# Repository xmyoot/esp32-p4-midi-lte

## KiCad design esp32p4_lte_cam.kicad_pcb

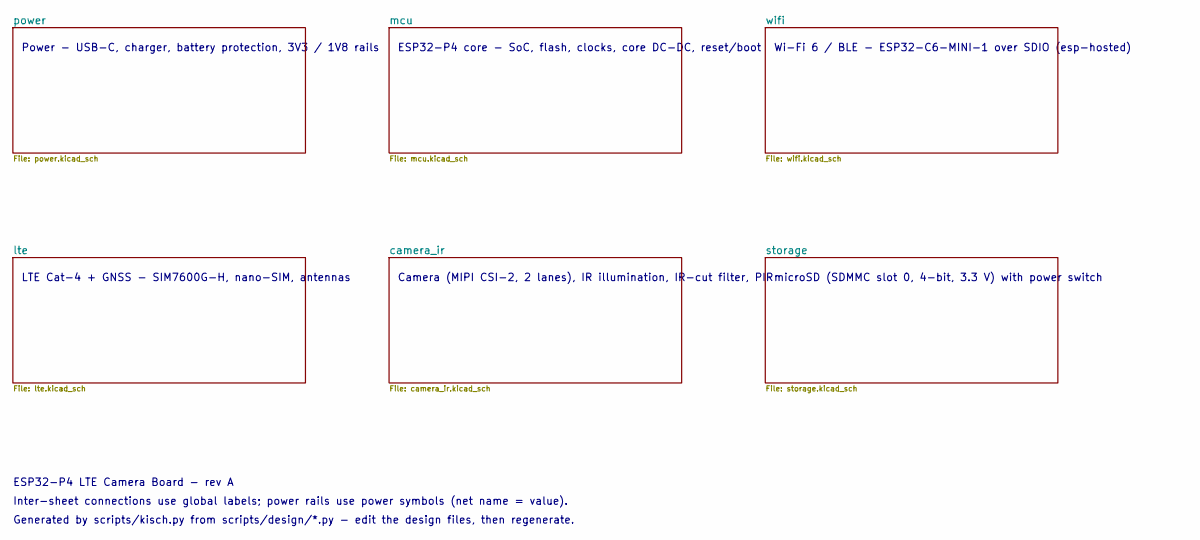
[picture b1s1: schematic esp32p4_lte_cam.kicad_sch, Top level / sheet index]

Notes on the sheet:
Power - USB-C, charger, battery protection, 3V3 / 1V8 rails
ESP32-P4 core - SoC, flash, clocks, core DC-DC, reset/boot
Wi-Fi 6 / BLE - ESP32-C6-MINI-1 over SDIO (esp-hosted)
LTE Cat-4 + GNSS - SIM7600G-H, nano-SIM, antennas
Camera (MIPI CSI-2, 2 lanes), IR illumination, IR-cut filter, PIR
microSD (SDMMC slot 0, 4-bit, 3.3 V) with power switch
ESP32-P4 LTE Camera Board - rev A
Inter-sheet connections use global labels; power rails use power symbols (net name = value).
Generated by scripts/kisch.py from scripts/design/*.py - edit the design files, then regenerate.

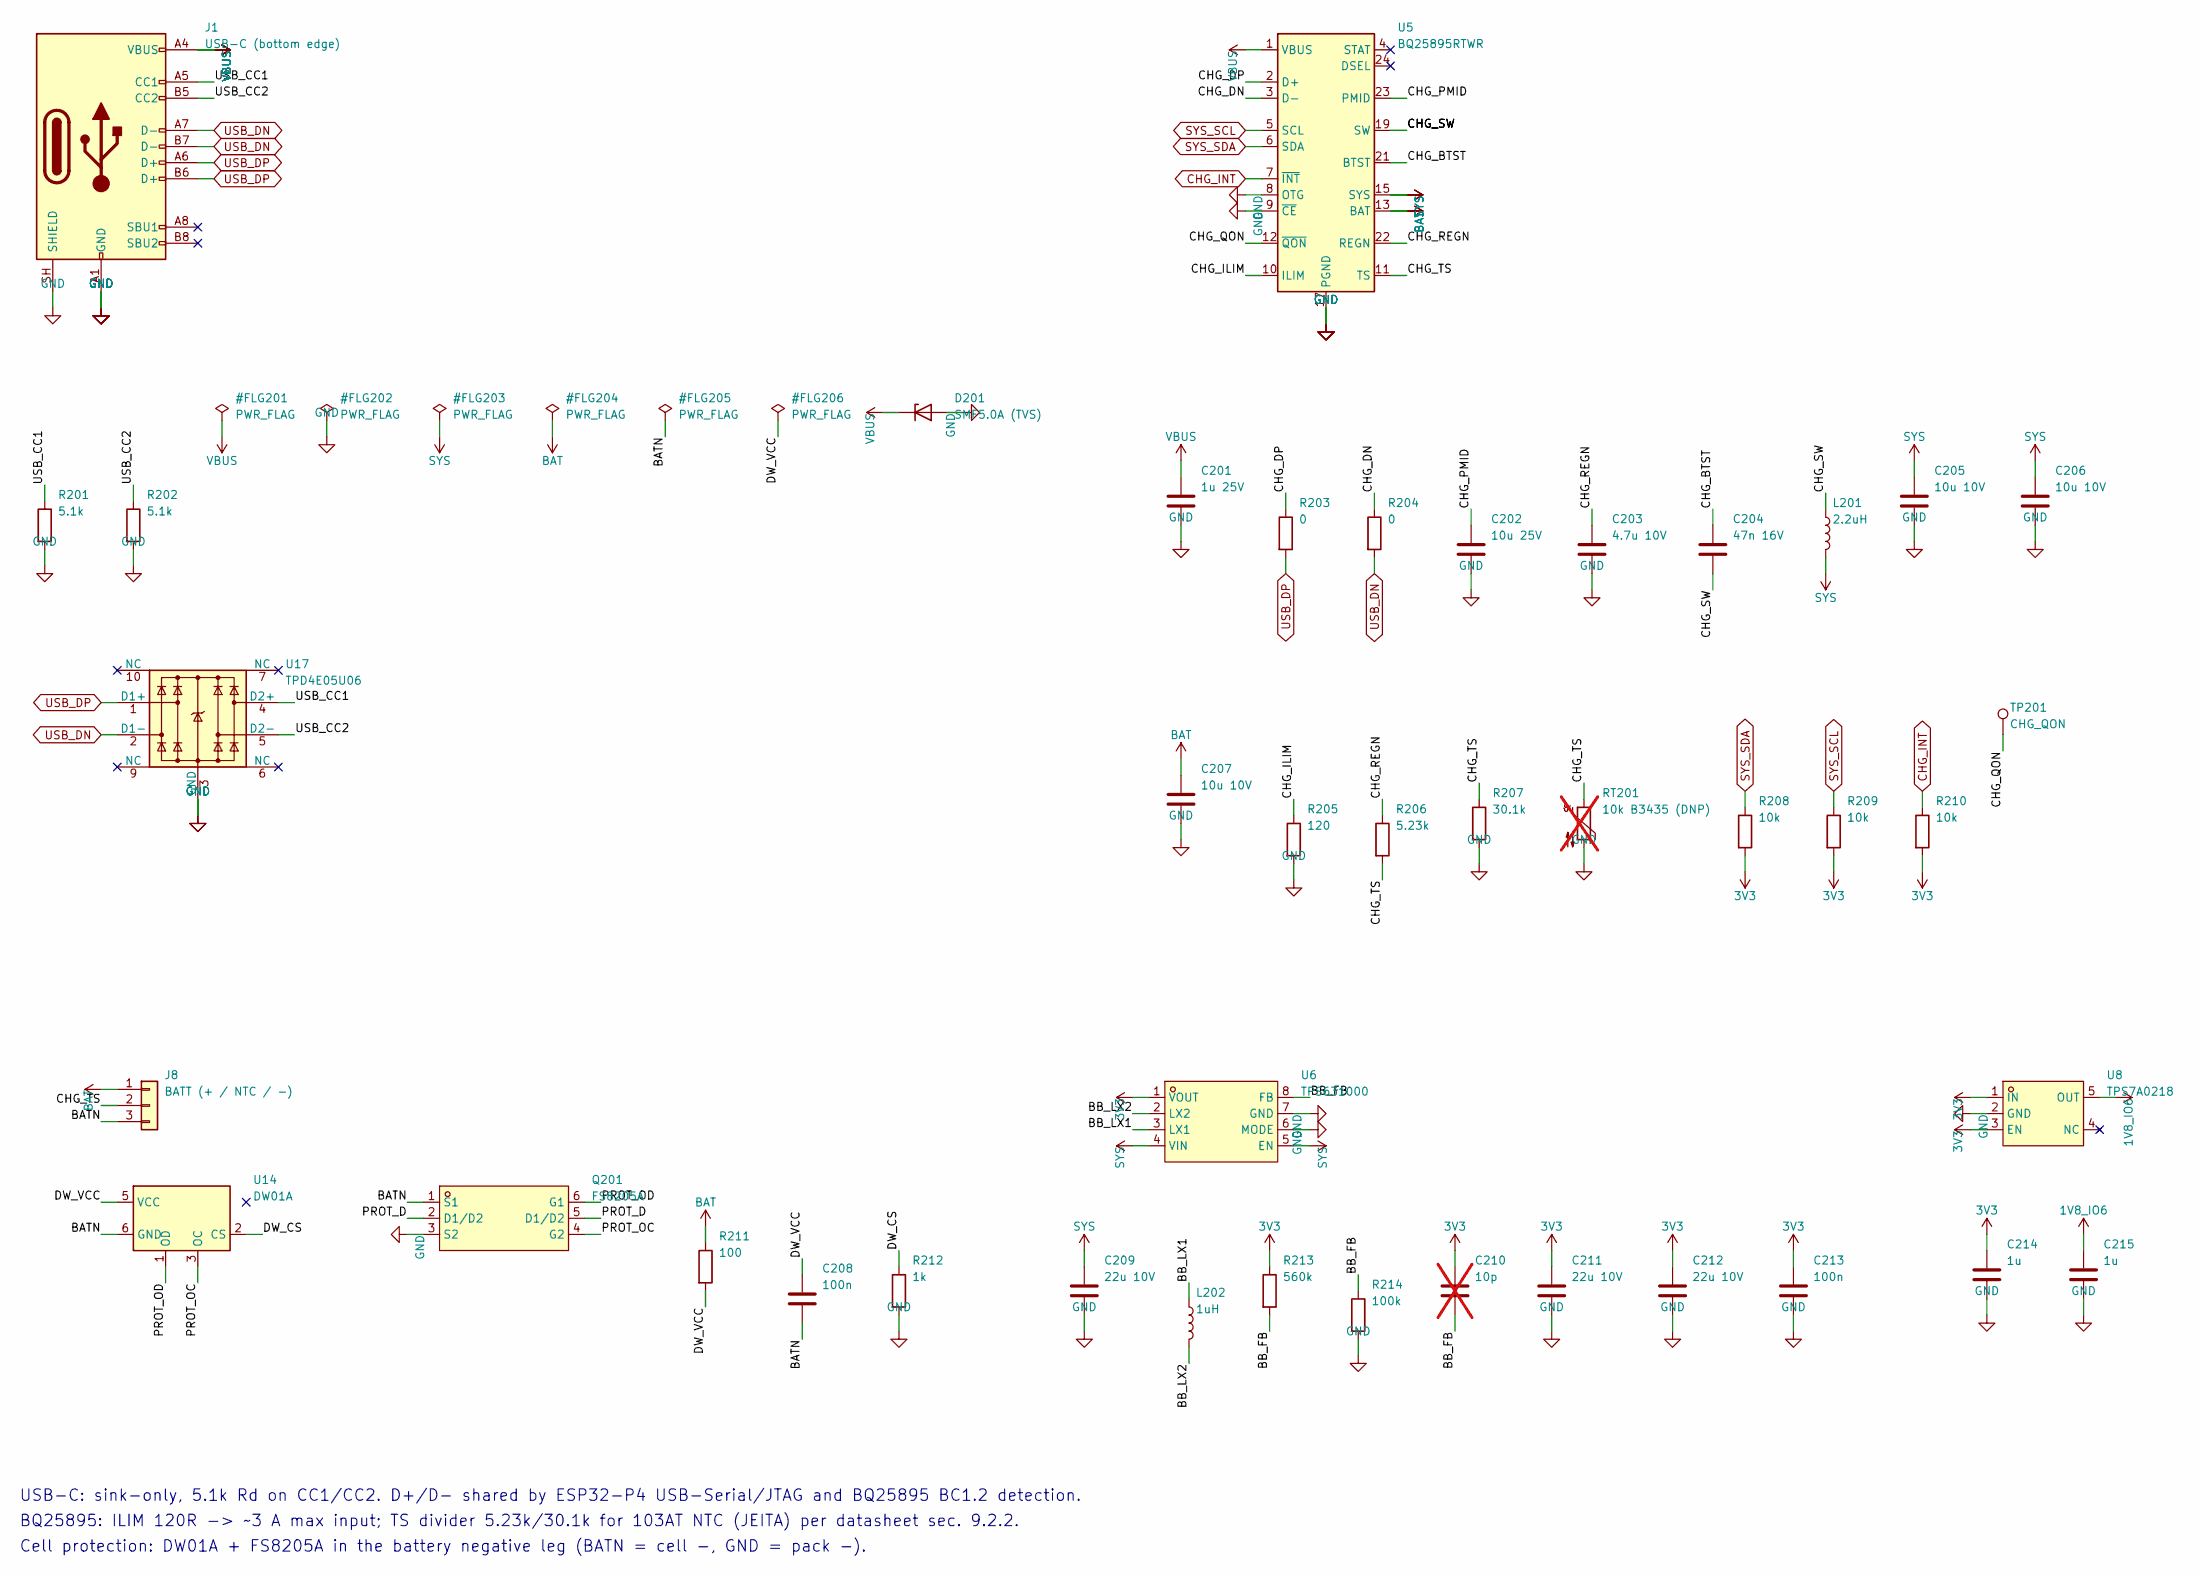
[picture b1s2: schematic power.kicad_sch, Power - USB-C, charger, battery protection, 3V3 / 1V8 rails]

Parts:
C201: 1u 25V; C_0603_1608Metric; MPN CL10A105KA8NNNC; LCSC C5673
C202: 10u 25V; C_0805_2012Metric; MPN CL21A106KAYNNNE; LCSC C15850
C203: 4.7u 10V; C_0603_1608Metric; MPN CL10A475KP8NNNC; LCSC C1705
C204: 47n 16V; C_0402_1005Metric; MPN CL05B473KO5NNNC; LCSC C307434
C205, C206, C207: 10u 10V; C_0805_2012Metric; MPN CL21A106KPFNNNE; LCSC C17024
C208, C213: 100n; C_0402_1005Metric; MPN CL05B104KO5NNNC; LCSC C1525
C209, C211, C212: 22u 10V; C_0805_2012Metric; MPN TCC0805X5R226M100FT; LCSC C380338
C210: 10p; C_0402_1005Metric; MPN CL05C100JB5NNNC; LCSC C32949; not fitted
C214, C215: 1u; C_0402_1005Metric; MPN CL05A105KA5NQNC; LCSC C52923
D201: SMF5.0A (TVS); D_SOD-123F; MPN SMF5.0A; LCSC C193402
J1: USB-C (bottom edge); USB_C_Receptacle_HRO_TYPE-C-31-M-12; MPN TYPE-C-31-M-12; LCSC C165948
J8: BATT (+ / NTC / -); JST_PH_S3B-PH-SM4-TB_1x03-1MP_P2.00mm_Horizontal; MPN S3B-PH-SM4-TB(LF)(SN); LCSC C265101
L201: 2.2uH; IND-SMD_L5.0-W5.0_SMNR5030; MPN SMNR5030-2R2N; LCSC C189797
L202: 1uH; L_1008_2520Metric; MPN WPN252012H1R0MT; LCSC C98348
Q201: FS8205A; SOT-23-6_L2.9-W1.6-P0.95-LS2.8-BR; MPN FS8205A; LCSC C2830320
R201, R202: 5.1k; R_0402_1005Metric; MPN 0402WGF5101TCE; LCSC C25905
R203, R204: 0; R_0402_1005Metric; MPN 0402WGF0000TCE; LCSC C17168
R205: 120; R_0402_1005Metric; MPN 0402WGF1200TCE; LCSC C25079
R206: 5.23k; R_0402_1005Metric; MPN FRC0402F5231TS; LCSC C2933105
R207: 30.1k; R_0402_1005Metric; MPN 0402WGF3012TCE; LCSC C29402
R208, R209, R210: 10k; R_0402_1005Metric; MPN 0402WGF1002TCE; LCSC C25744
R211: 100; R_0402_1005Metric; MPN 0402WGF1000TCE; LCSC C25076
R212: 1k; R_0402_1005Metric; MPN 0402WGF1001TCE; LCSC C11702
R213: 560k; R_0402_1005Metric; MPN RC0402FR-07560KL; LCSC C137958
R214: 100k; R_0402_1005Metric; MPN 0402WGF1003TCE; LCSC C25741
RT201: 10k B3435 (DNP); R_0603_1608Metric; MPN NCP18XH103F03RB; LCSC C13564; not fitted
TP201: CHG_QON; TestPoint_Pad_D1.0mm
U5: BQ25895RTWR; Texas_RTW_WQFN-24-1EP_4x4mm_P0.5mm_EP2.7x2.7mm_ThermalVias; MPN BQ25895RTWR; LCSC C80200
U6: TPS631000; SOT-583-8_L2.1-W1.2-P0.50-LS1.6-BL; MPN TPS631000DRLR; LCSC C5219190
U8: TPS7A0218; SOT-23-5_L3.0-W1.7-P0.95-LS2.8-BL; MPN TPS7A0218DBVR; LCSC C5144851
U14: DW01A; SOT-23-6; MPN DW01A; LCSC C351410
U17: TPD4E05U06; USON-10_2.5x1.0mm_P0.5mm; MPN TPD4E05U06DQAR; LCSC C138714

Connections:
1V8_IO6: C215.1, U8.5 (OUT); also elsewhere on the board
3V3: C210.1, C211.1, C212.1, C213.1, C214.1, R208.2, R209.2, R210.2, R213.1, U6.1 (VOUT), U8.1 (IN), U8.3 (EN); also elsewhere on the board
/power/BATN: C208.2, J8.3, Q201.1 (S1), U14.6 (GND)
/power/BB_FB: C210.2, R213.2, R214.1, U6.8 (FB)
/power/BB_LX1: L202.1, U6.3 (LX1)
/power/BB_LX2: L202.2, U6.2 (LX2)
/power/CHG_BTST: C204.1, U5.21 (BTST)
/power/CHG_DN: R204.1, U5.3 (D-)
/power/CHG_DP: R203.1, U5.2 (D+)
/power/CHG_ILIM: R205.1, U5.10 (ILIM)
/power/CHG_PMID: C202.1, U5.23 (PMID)
/power/CHG_QON: TP201.1, U5.12 (~QON)
/power/CHG_REGN: C203.1, R206.1, U5.22 (REGN)
/power/CHG_SW: C204.2, L201.1, U5.19 (SW), U5.20 (SW)
/power/CHG_TS: J8.2, R206.2, R207.1, RT201.1, U5.11 (TS)
/power/DW_CS: R212.1, U14.2 (CS)
/power/DW_VCC: C208.1, R211.2, U14.5 (VCC)
/power/PROT_D: Q201.2 (D1/D2), Q201.5 (D1/D2)
/power/PROT_OC: Q201.4 (G2), U14.3 (OC)
/power/PROT_OD: Q201.6 (G1), U14.1 (OD)
/power/USB_CC1: J1.A5 (CC1), R201.1, U17.4 (D2+)
/power/USB_CC2: J1.B5 (CC2), R202.1, U17.5 (D2-)
BAT: C207.1, J8.1, R211.1, U5.13 (BAT), U5.14 (BAT)
CHG_INT: R210.1, U5.7 (~INT); also elsewhere on the board
GND: C201.2, C202.2, C203.2, C205.2, C206.2, C207.2, C209.2, C211.2, C212.2, C213.2, C214.2, C215.2, D201.2 (A), J1.A1 (GND), J1.A12 (GND), J1.B1 (GND), J1.B12 (GND), J1.SH (SHIELD), Q201.3 (S2), R201.2, R202.2, R205.2, R207.2, R212.2, R214.2, RT201.2, U5.8 (OTG), U5.9 (~CE), U5.17 (PGND), U5.18 (PGND), U5.25 (PGND), U6.6 (MODE), U6.7 (GND), U8.2 (GND), U17.3 (GND), U17.8 (GND); also elsewhere on the board
SYS: C205.1, C206.1, C209.1, L201.2, U5.15 (SYS), U5.16 (SYS), U6.4 (VIN), U6.5 (EN); also elsewhere on the board
SYS_SCL: R209.1, U5.5 (SCL); also elsewhere on the board
SYS_SDA: R208.1, U5.6 (SDA); also elsewhere on the board
USB_DN: J1.A7 (D-), J1.B7 (D-), R204.2, U17.2 (D1-); also elsewhere on the board
USB_DP: J1.A6 (D+), J1.B6 (D+), R203.2, U17.1 (D1+); also elsewhere on the board
VBUS: C201.1, D201.1 (K), J1.A4 (VBUS), J1.A9 (VBUS), J1.B4 (VBUS), J1.B9 (VBUS), U5.1 (VBUS)

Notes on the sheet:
USB-C: sink-only, 5.1k Rd on CC1/CC2. D+/D- shared by ESP32-P4 USB-Serial/JTAG and BQ25895 BC1.2 detection.
BQ25895: ILIM 120R -> ~3 A max input; TS divider 5.23k/30.1k for 103AT NTC (JEITA) per datasheet sec. 9.2.2.
Cell protection: DW01A + FS8205A in the battery negative leg (BATN = cell -, GND = pack -).

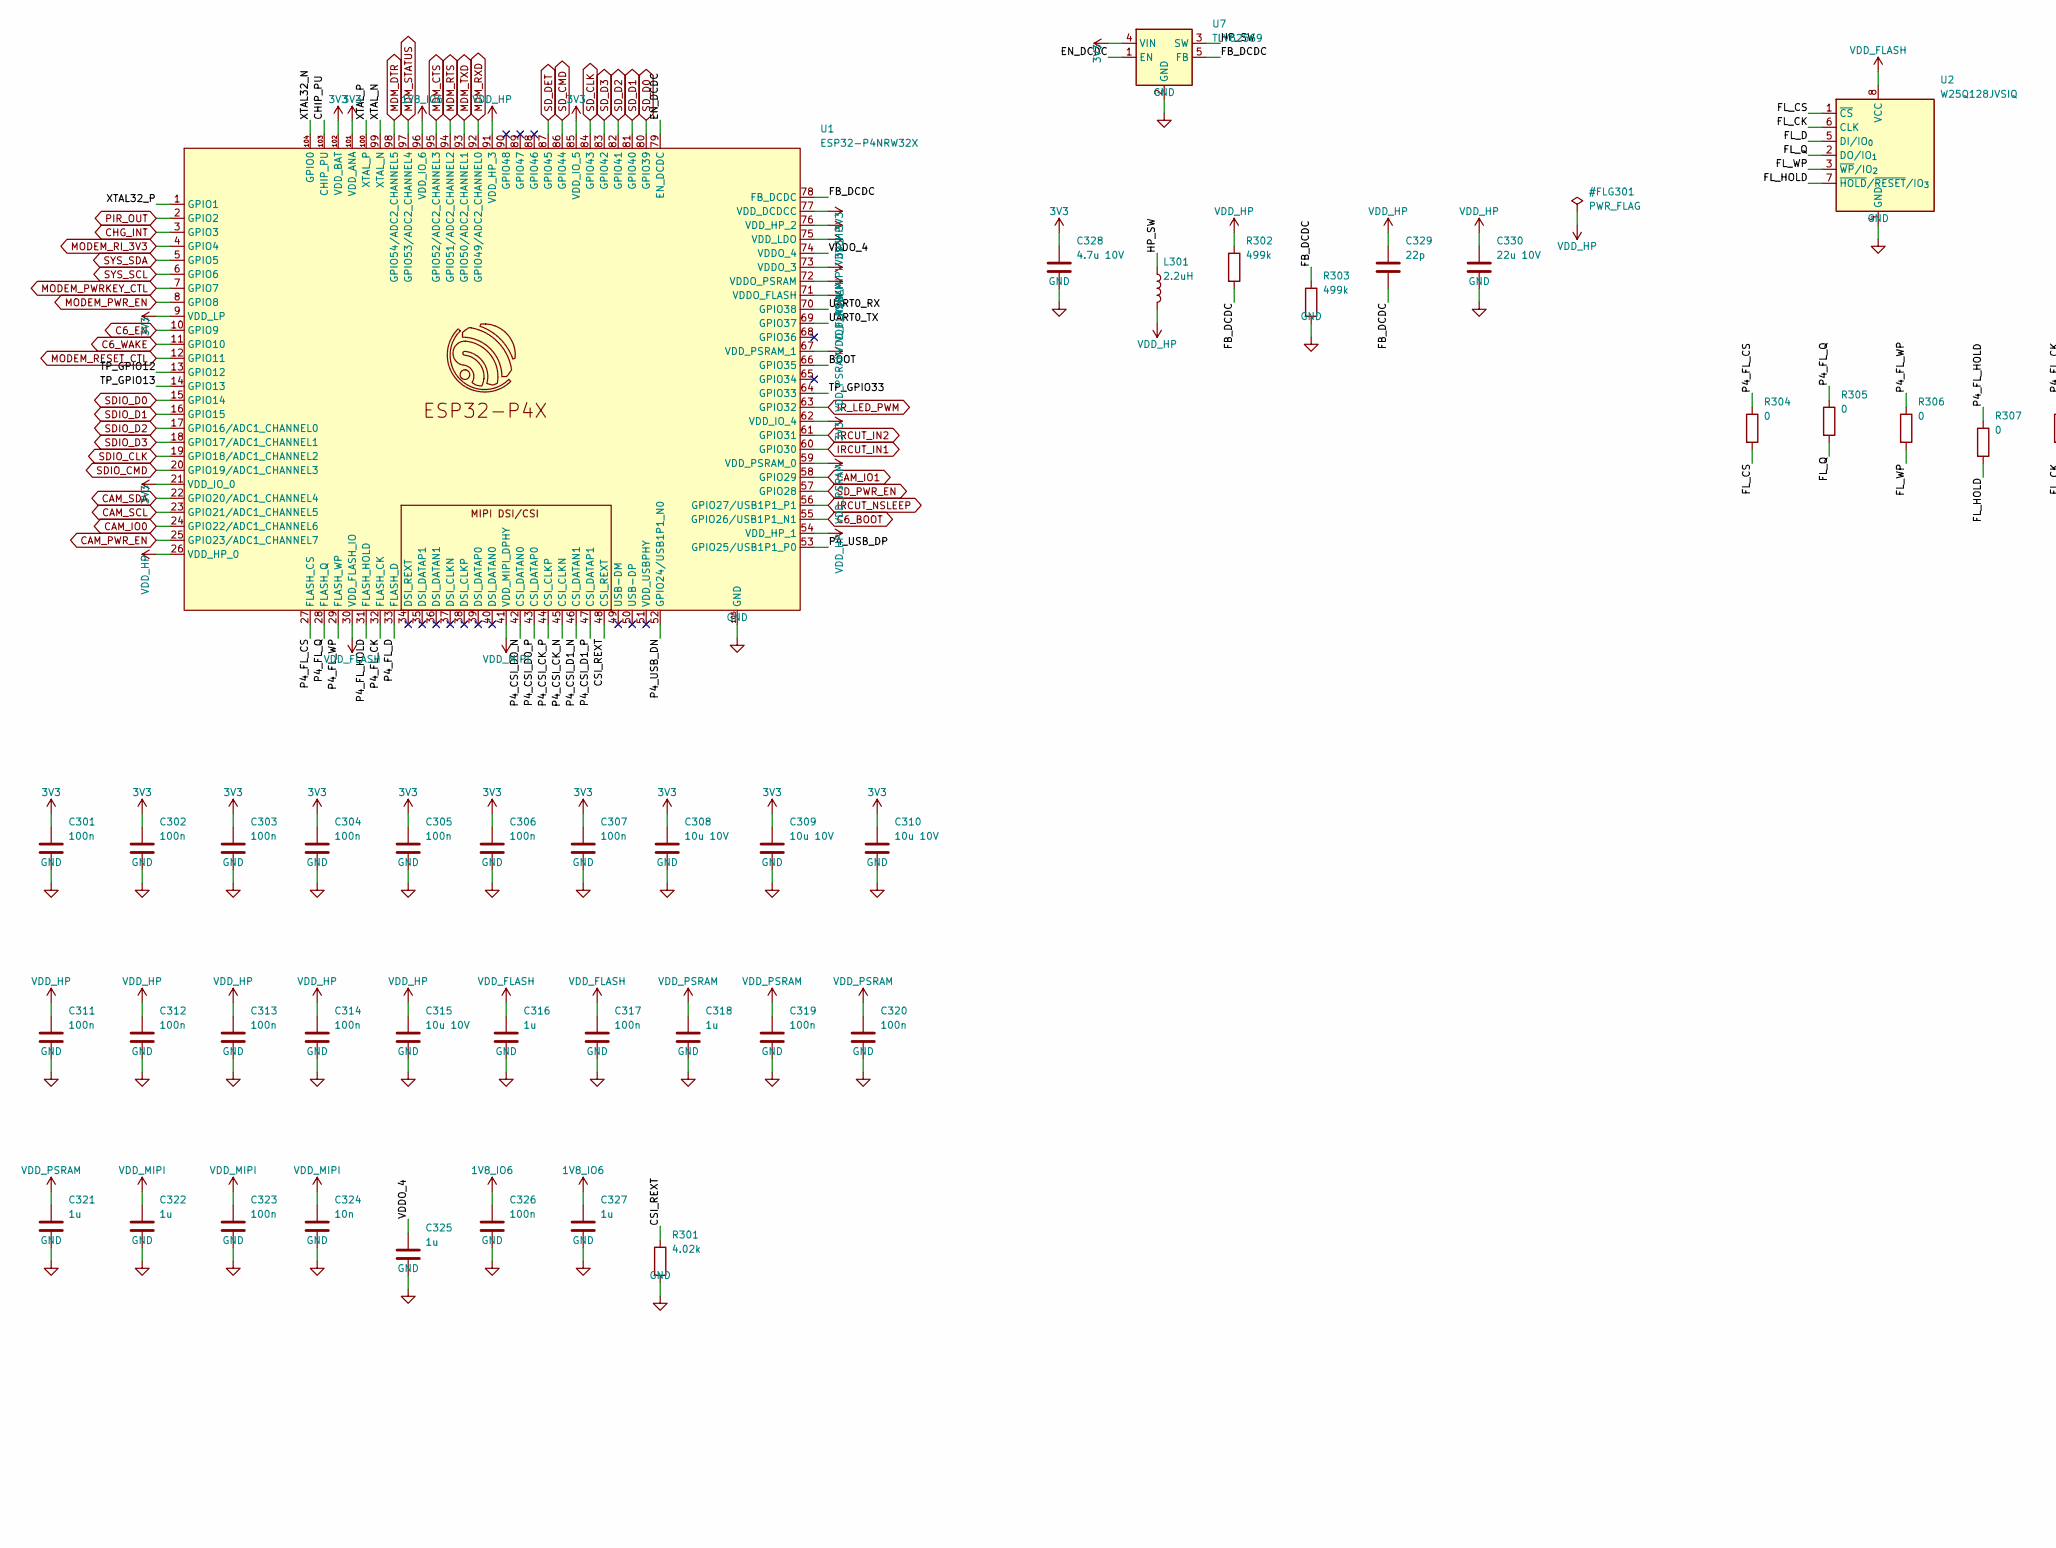
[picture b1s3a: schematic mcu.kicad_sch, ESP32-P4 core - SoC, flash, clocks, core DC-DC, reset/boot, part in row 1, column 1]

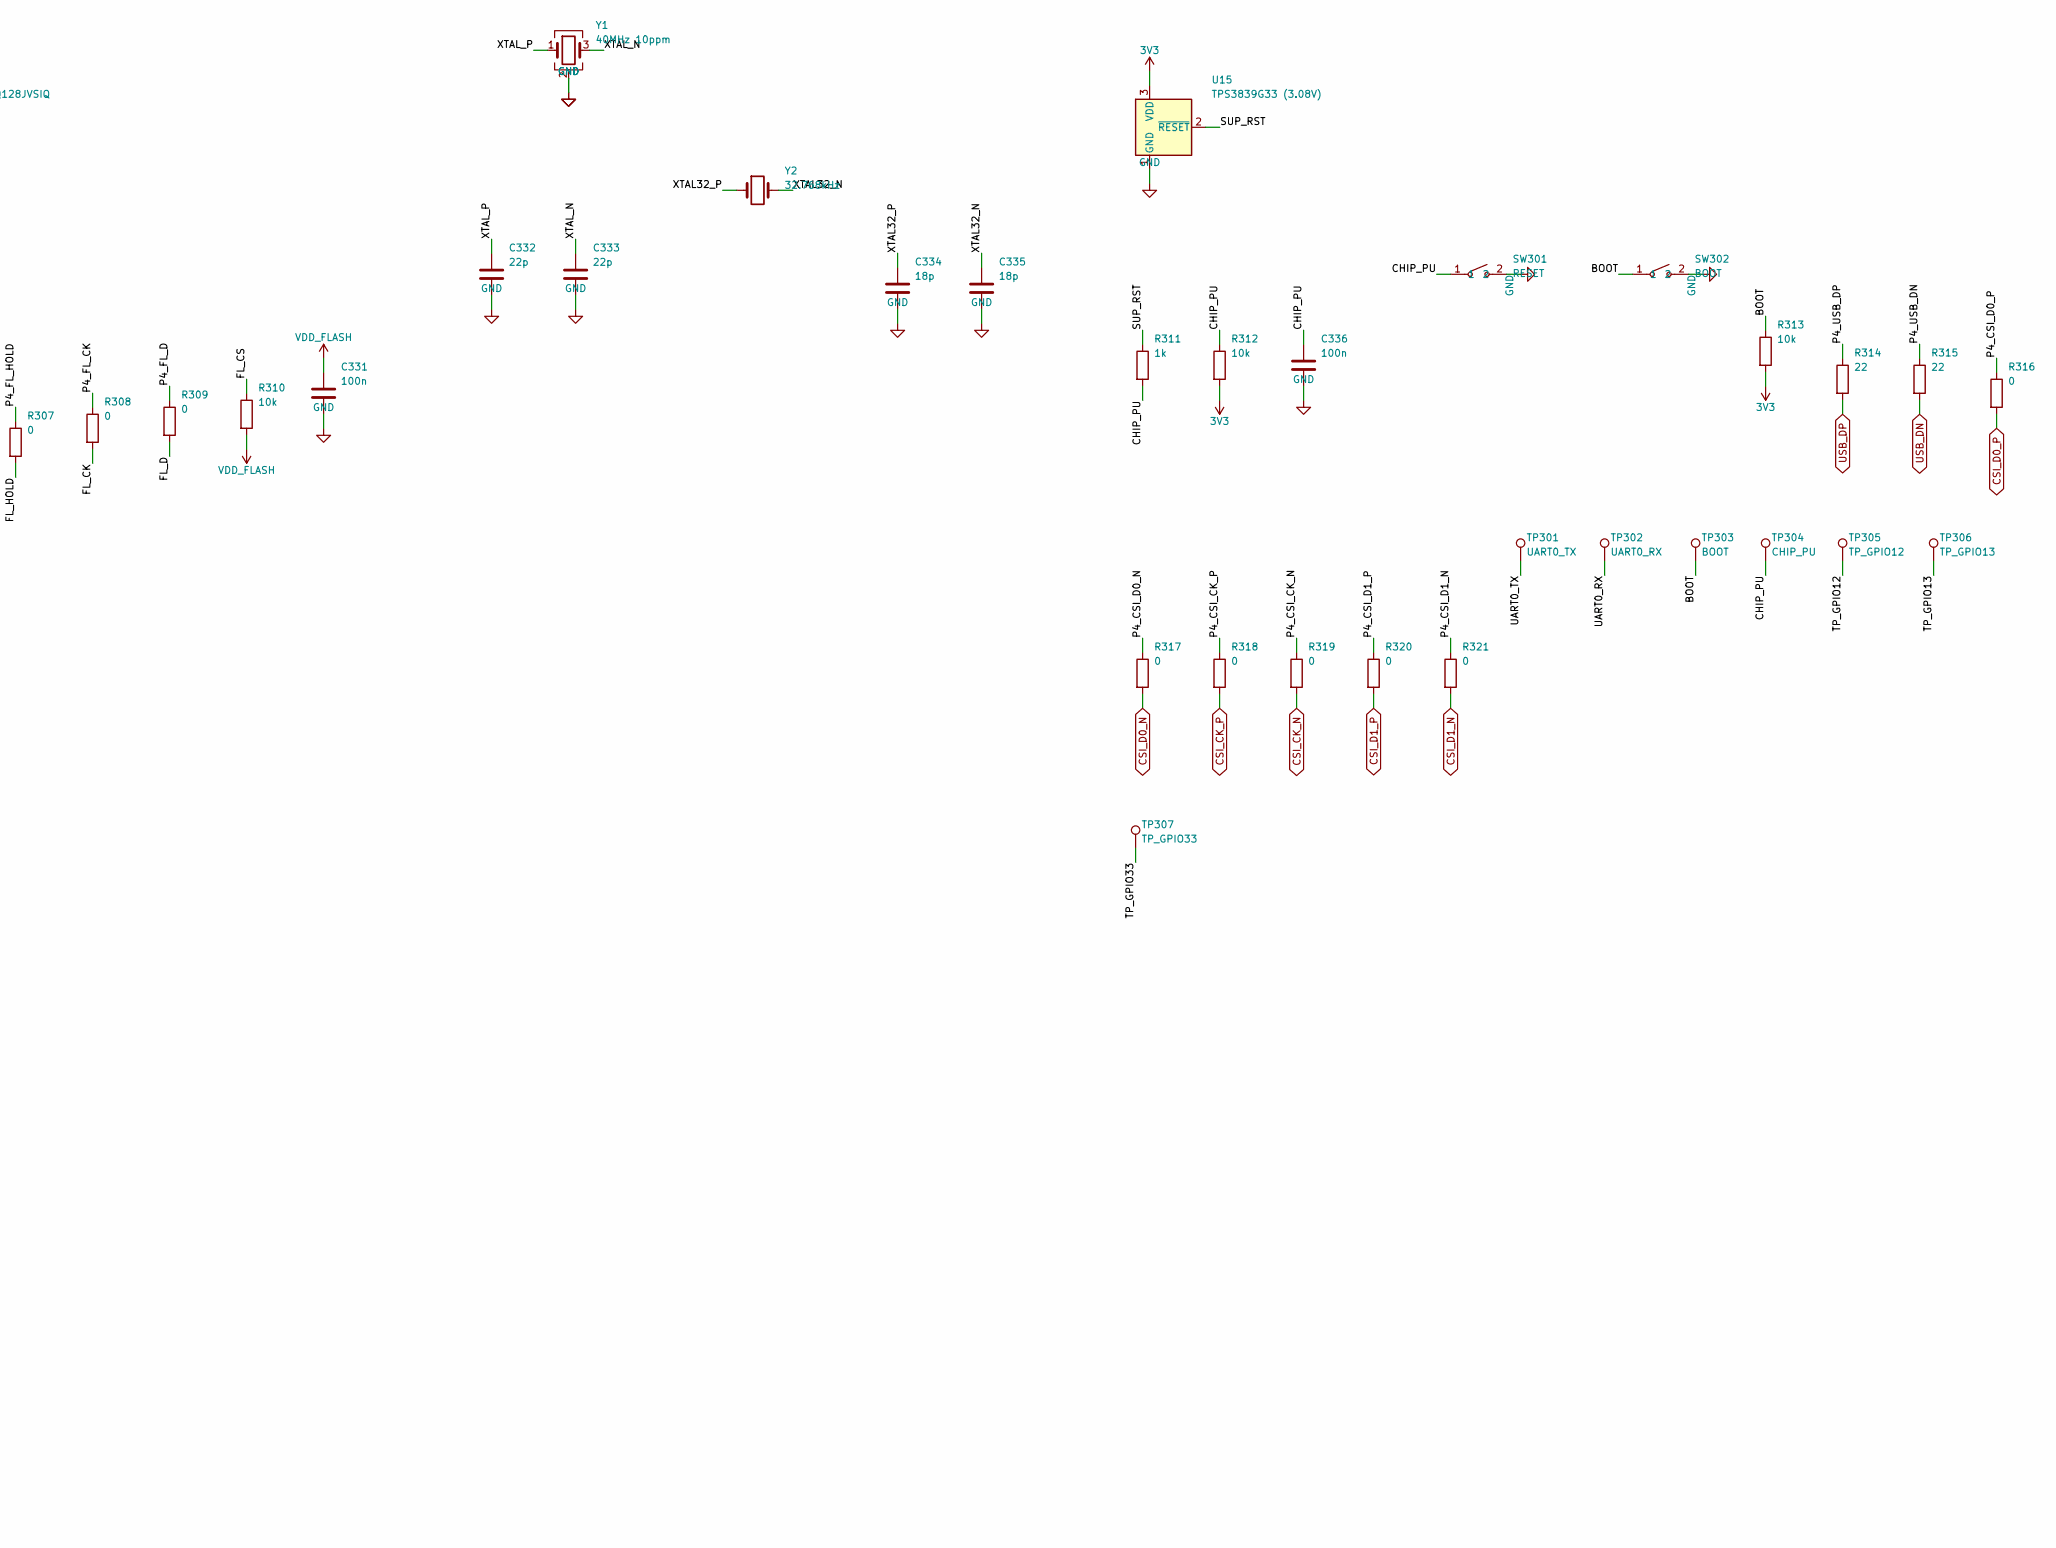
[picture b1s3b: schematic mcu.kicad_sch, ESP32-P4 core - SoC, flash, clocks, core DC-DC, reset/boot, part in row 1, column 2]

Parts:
C301, C302, C303, C304, C305, C306, C307, C311, C312, C313, C314, C317, C319, C320, C323, C326, C331, C336: 100n; C_0402_1005Metric; MPN CL05B104KO5NNNC; LCSC C1525
C308, C309, C310, C315: 10u 10V; C_0603_1608Metric; MPN CL10A106KP8NNNC; LCSC C19702
C316, C318, C321, C322, C325, C327: 1u; C_0402_1005Metric; MPN CL05A105KA5NQNC; LCSC C52923
C324: 10n; C_0402_1005Metric; MPN CL05B103KB5NNNC; LCSC C15195
C328: 4.7u 10V; C_0603_1608Metric; MPN CL10A475KP8NNNC; LCSC C1705
C329, C332, C333: 22p; C_0402_1005Metric; MPN 0402CG220J500NT; LCSC C1555
C330: 22u 10V; C_0805_2012Metric; MPN TCC0805X5R226M100FT; LCSC C380338
C334, C335: 18p; C_0402_1005Metric; MPN 0402CG180J500NT; LCSC C1549
L301: 2.2uH; L_1008_2520Metric; MPN FTC252012S2R2MBCA; LCSC C5832372
R301: 4.02k; R_0402_1005Metric; MPN 0402WGF4021TCE; LCSC C43251
R302, R303: 499k; R_0402_1005Metric; MPN FRC0402F4993TS; LCSC C2998054
R304, R305, R306, R307, R308, R309, R316, R317, R318, R319, R320, R321: 0; R_0402_1005Metric; MPN 0402WGF0000TCE; LCSC C17168
R310, R312, R313: 10k; R_0402_1005Metric; MPN 0402WGF1002TCE; LCSC C25744
R311: 1k; R_0402_1005Metric; MPN 0402WGF1001TCE; LCSC C11702
R314, R315: 22; R_0402_1005Metric; MPN 0402WGF220JTCE; LCSC C25092
SW301: RESET; SW-SMD_L4.0-W2.9-P4.15-EH; MPN TS-1088C-02026; LCSC C455278
SW302: BOOT; SW-SMD_L4.0-W2.9-P4.15-EH; MPN TS-1088C-02026; LCSC C455278
TP301: UART0_TX; TestPoint_Pad_D1.0mm
TP302: UART0_RX; TestPoint_Pad_D1.0mm
TP303: BOOT; TestPoint_Pad_D1.0mm
TP304: CHIP_PU; TestPoint_Pad_D1.0mm
TP305: TP_GPIO12; TestPoint_Pad_D1.0mm
TP306: TP_GPIO13; TestPoint_Pad_D1.0mm
TP307: TP_GPIO33; TestPoint_Pad_D1.0mm
U1: ESP32-P4NRW32X; ESP32-P4; MPN ESP32-P4NRW32X; LCSC C54540373
U2: W25Q128JVSIQ; SOIC-8_5.3x5.3mm_P1.27mm; MPN W25Q128JVSIQ; LCSC C97521
U7: TLV62569; SOT-23-5; MPN TLV62569DBVR; LCSC C141836
U15: TPS3839G33 (3.08V); SOT-23; MPN TPS3839G33DBZR; LCSC C485802
Y1: 40MHz 10ppm; Crystal_SMD_3225-4Pin_3.2x2.5mm; MPN X322540MPB4SI; LCSC C9010
Y2: 32.768kHz; Crystal_SMD_3215-2Pin_3.2x1.5mm; MPN Q13FC13500004; LCSC C32346

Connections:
1V8_IO6: C326.1, C327.1, U1.96 (VDD_IO_6); also elsewhere on the board
3V3: C301.1, C302.1, C303.1, C304.1, C305.1, C306.1, C307.1, C308.1, C309.1, C310.1, C328.1, R312.2, R313.2, U1.9 (VDD_LP), U1.21 (VDD_IO_0), U1.62 (VDD_IO_4), U1.75 (VDD_LDO), U1.77 (VDD_DCDCC), U1.85 (VDD_IO_5), U1.101 (VDD_ANA), U1.102 (VDD_BAT), U7.4 (VIN), U15.3 (VDD); also elsewhere on the board
/mcu/BOOT: R313.1, SW302.1, TP303.1, U1.66 (GPIO35)
/mcu/CHIP_PU: C336.1, R311.2, R312.1, SW301.1, TP304.1, U1.103 (CHIP_PU)
/mcu/CSI_REXT: R301.1, U1.48 (CSI_REXT)
/mcu/EN_DCDC: U1.79 (EN_DCDC), U7.1 (EN)
/mcu/FB_DCDC: C329.2, R302.2, R303.1, U1.78 (FB_DCDC), U7.5 (FB)
/mcu/FL_CK: R308.2, U2.6 (CLK)
/mcu/FL_CS: R304.2, R310.1, U2.1 (~CS)
/mcu/FL_D: R309.2, U2.5 (DI/IO_{0})
/mcu/FL_HOLD: R307.2, U2.7 (~HOLD/~RESET/IO_{3})
/mcu/FL_Q: R305.2, U2.2 (DO/IO_{1})
/mcu/FL_WP: R306.2, U2.3 (~WP/IO_{2})
/mcu/HP_SW: L301.1, U7.3 (SW)
/mcu/P4_CSI_CK_N: R319.1, U1.45 (CSI_CLKN)
/mcu/P4_CSI_CK_P: R318.1, U1.44 (CSI_CLKP)
/mcu/P4_CSI_D0_N: R317.1, U1.42 (CSI_DATAN0)
/mcu/P4_CSI_D0_P: R316.1, U1.43 (CSI_DATAP0)
/mcu/P4_CSI_D1_N: R321.1, U1.46 (CSI_DATAN1)
/mcu/P4_CSI_D1_P: R320.1, U1.47 (CSI_DATAP1)
/mcu/P4_FL_CK: R308.1, U1.32 (FLASH_CK)
/mcu/P4_FL_CS: R304.1, U1.27 (FLASH_CS)
/mcu/P4_FL_D: R309.1, U1.33 (FLASH_D)
/mcu/P4_FL_HOLD: R307.1, U1.31 (FLASH_HOLD)
/mcu/P4_FL_Q: R305.1, U1.28 (FLASH_Q)
/mcu/P4_FL_WP: R306.1, U1.29 (FLASH_WP)
/mcu/P4_USB_DN: R315.1, U1.52 (GPIO24/USB1P1_N0)
/mcu/P4_USB_DP: R314.1, U1.53 (GPIO25/USB1P1_P0)
/mcu/SUP_RST: R311.1, U15.2 (~RESET)
/mcu/TP_GPIO12: TP305.1, U1.13 (GPIO12)
/mcu/TP_GPIO13: TP306.1, U1.14 (GPIO13)
/mcu/TP_GPIO33: TP307.1, U1.64 (GPIO33)
/mcu/UART0_RX: TP302.1, U1.70 (GPIO38)
/mcu/UART0_TX: TP301.1, U1.69 (GPIO37)
/mcu/VDDO_4: C325.1, U1.74 (VDDO_4)
/mcu/XTAL32_N: C335.1, U1.104 (GPIO0), Y2.2
/mcu/XTAL32_P: C334.1, U1.1 (GPIO1), Y2.1
/mcu/XTAL_N: C333.1, U1.99 (XTAL_N), Y1.3
/mcu/XTAL_P: C332.1, U1.100 (XTAL_P), Y1.1
C6_BOOT: U1.55 (GPIO26/USB1P1_N1); also elsewhere on the board
C6_EN: U1.10 (GPIO9); also elsewhere on the board
C6_WAKE: U1.11 (GPIO10); also elsewhere on the board
CAM_IO0: U1.24 (GPIO22/ADC1_CHANNEL6); also elsewhere on the board
CAM_IO1: U1.58 (GPIO29); also elsewhere on the board
CAM_PWR_EN: U1.25 (GPIO23/ADC1_CHANNEL7); also elsewhere on the board
CAM_SCL: U1.23 (GPIO21/ADC1_CHANNEL5); also elsewhere on the board
CAM_SDA: U1.22 (GPIO20/ADC1_CHANNEL4); also elsewhere on the board
CHG_INT: U1.3 (GPIO3); also elsewhere on the board
CSI_CK_N: R319.2; also elsewhere on the board
CSI_CK_P: R318.2; also elsewhere on the board
CSI_D0_N: R317.2; also elsewhere on the board
CSI_D0_P: R316.2; also elsewhere on the board
CSI_D1_N: R321.2; also elsewhere on the board
CSI_D1_P: R320.2; also elsewhere on the board
GND: C301.2, C302.2, C303.2, C304.2, C305.2, C306.2, C307.2, C308.2, C309.2, C310.2, C311.2, C312.2, C313.2, C314.2, C315.2, C316.2, C317.2, C318.2, C319.2, C320.2, C321.2, C322.2, C323.2, C324.2, C325.2, C326.2, C327.2, C328.2, C330.2, C331.2, C332.2, C333.2, C334.2, C335.2, C336.2, R301.2, R303.2, SW301.2, SW302.2, U1.105 (GND), U2.4 (GND), U7.2 (GND), U15.1 (GND), Y1.2 (G), Y1.4 (G); also elsewhere on the board
IRCUT_IN1: U1.60 (GPIO30); also elsewhere on the board
IRCUT_IN2: U1.61 (GPIO31); also elsewhere on the board
IRCUT_NSLEEP: U1.56 (GPIO27/USB1P1_P1); also elsewhere on the board
IR_LED_PWM: U1.63 (GPIO32); also elsewhere on the board
MDM_CTS: U1.95 (GPIO52/ADC2_CHANNEL3); also elsewhere on the board
MDM_DTR: U1.98 (GPIO54/ADC2_CHANNEL5); also elsewhere on the board
MDM_RTS: U1.94 (GPIO51/ADC2_CHANNEL2); also elsewhere on the board
MDM_RXD: U1.92 (GPIO49/ADC2_CHANNEL0); also elsewhere on the board
MDM_STATUS: U1.97 (GPIO53/ADC2_CHANNEL4); also elsewhere on the board
MDM_TXD: U1.93 (GPIO50/ADC2_CHANNEL1); also elsewhere on the board
MODEM_PWRKEY_CTL: U1.7 (GPIO7); also elsewhere on the board
MODEM_PWR_EN: U1.8 (GPIO8); also elsewhere on the board
MODEM_RESET_CTL: U1.12 (GPIO11); also elsewhere on the board
MODEM_RI_3V3: U1.4 (GPIO4); also elsewhere on the board
PIR_OUT: U1.2 (GPIO2); also elsewhere on the board
SDIO_CLK: U1.19 (GPIO18/ADC1_CHANNEL2); also elsewhere on the board
SDIO_CMD: U1.20 (GPIO19/ADC1_CHANNEL3); also elsewhere on the board
SDIO_D0: U1.15 (GPIO14); also elsewhere on the board
SDIO_D1: U1.16 (GPIO15); also elsewhere on the board
SDIO_D2: U1.17 (GPIO16/ADC1_CHANNEL0); also elsewhere on the board
SDIO_D3: U1.18 (GPIO17/ADC1_CHANNEL1); also elsewhere on the board
SD_CLK: U1.84 (GPIO43); also elsewhere on the board
SD_CMD: U1.86 (GPIO44); also elsewhere on the board
SD_D0: U1.80 (GPIO39); also elsewhere on the board
SD_D1: U1.81 (GPIO40); also elsewhere on the board
SD_D2: U1.82 (GPIO41); also elsewhere on the board
SD_D3: U1.83 (GPIO42); also elsewhere on the board
SD_DET: U1.87 (GPIO45); also elsewhere on the board
SD_PWR_EN: U1.57 (GPIO28); also elsewhere on the board
SYS_SCL: U1.6 (GPIO6); also elsewhere on the board
SYS_SDA: U1.5 (GPIO5); also elsewhere on the board
USB_DN: R315.2; also elsewhere on the board
USB_DP: R314.2; also elsewhere on the board
VDD_FLASH: C316.1, C317.1, C331.1, R310.2, U1.30 (VDD_FLASH_IO), U1.71 (VDDO_FLASH), U2.8 (VCC)
VDD_HP: C311.1, C312.1, C313.1, C314.1, C315.1, C329.1, C330.1, L301.2, R302.1, U1.26 (VDD_HP_0), U1.54 (VDD_HP_1), U1.76 (VDD_HP_2), U1.91 (VDD_HP_3)
VDD_MIPI: C322.1, C323.1, C324.1, U1.41 (VDD_MIPI_DPHY), U1.73 (VDDO_3)
VDD_PSRAM: C318.1, C319.1, C320.1, C321.1, U1.59 (VDD_PSRAM_0), U1.67 (VDD_PSRAM_1), U1.72 (VDDO_PSRAM)

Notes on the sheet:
Chip rev v3.x (ESP32-P4NRW32X): VDD_HP_1 on pin 54; DC-DC feedback 499k/499k/22pF populated (HDG fig. 5).
VDD_MIPI_DPHY fed from internal VDDO_3 (2.5 V) as on ESP32-P4-Function-EV v1.5.2. VDD_USBPHY unused (HS PHY not used).
VDD_IO_6 = 1.8 V: GPIO49-54 talk to the SIM7600 UART natively. Keep these pins hi-Z while VBAT_LTE is off.

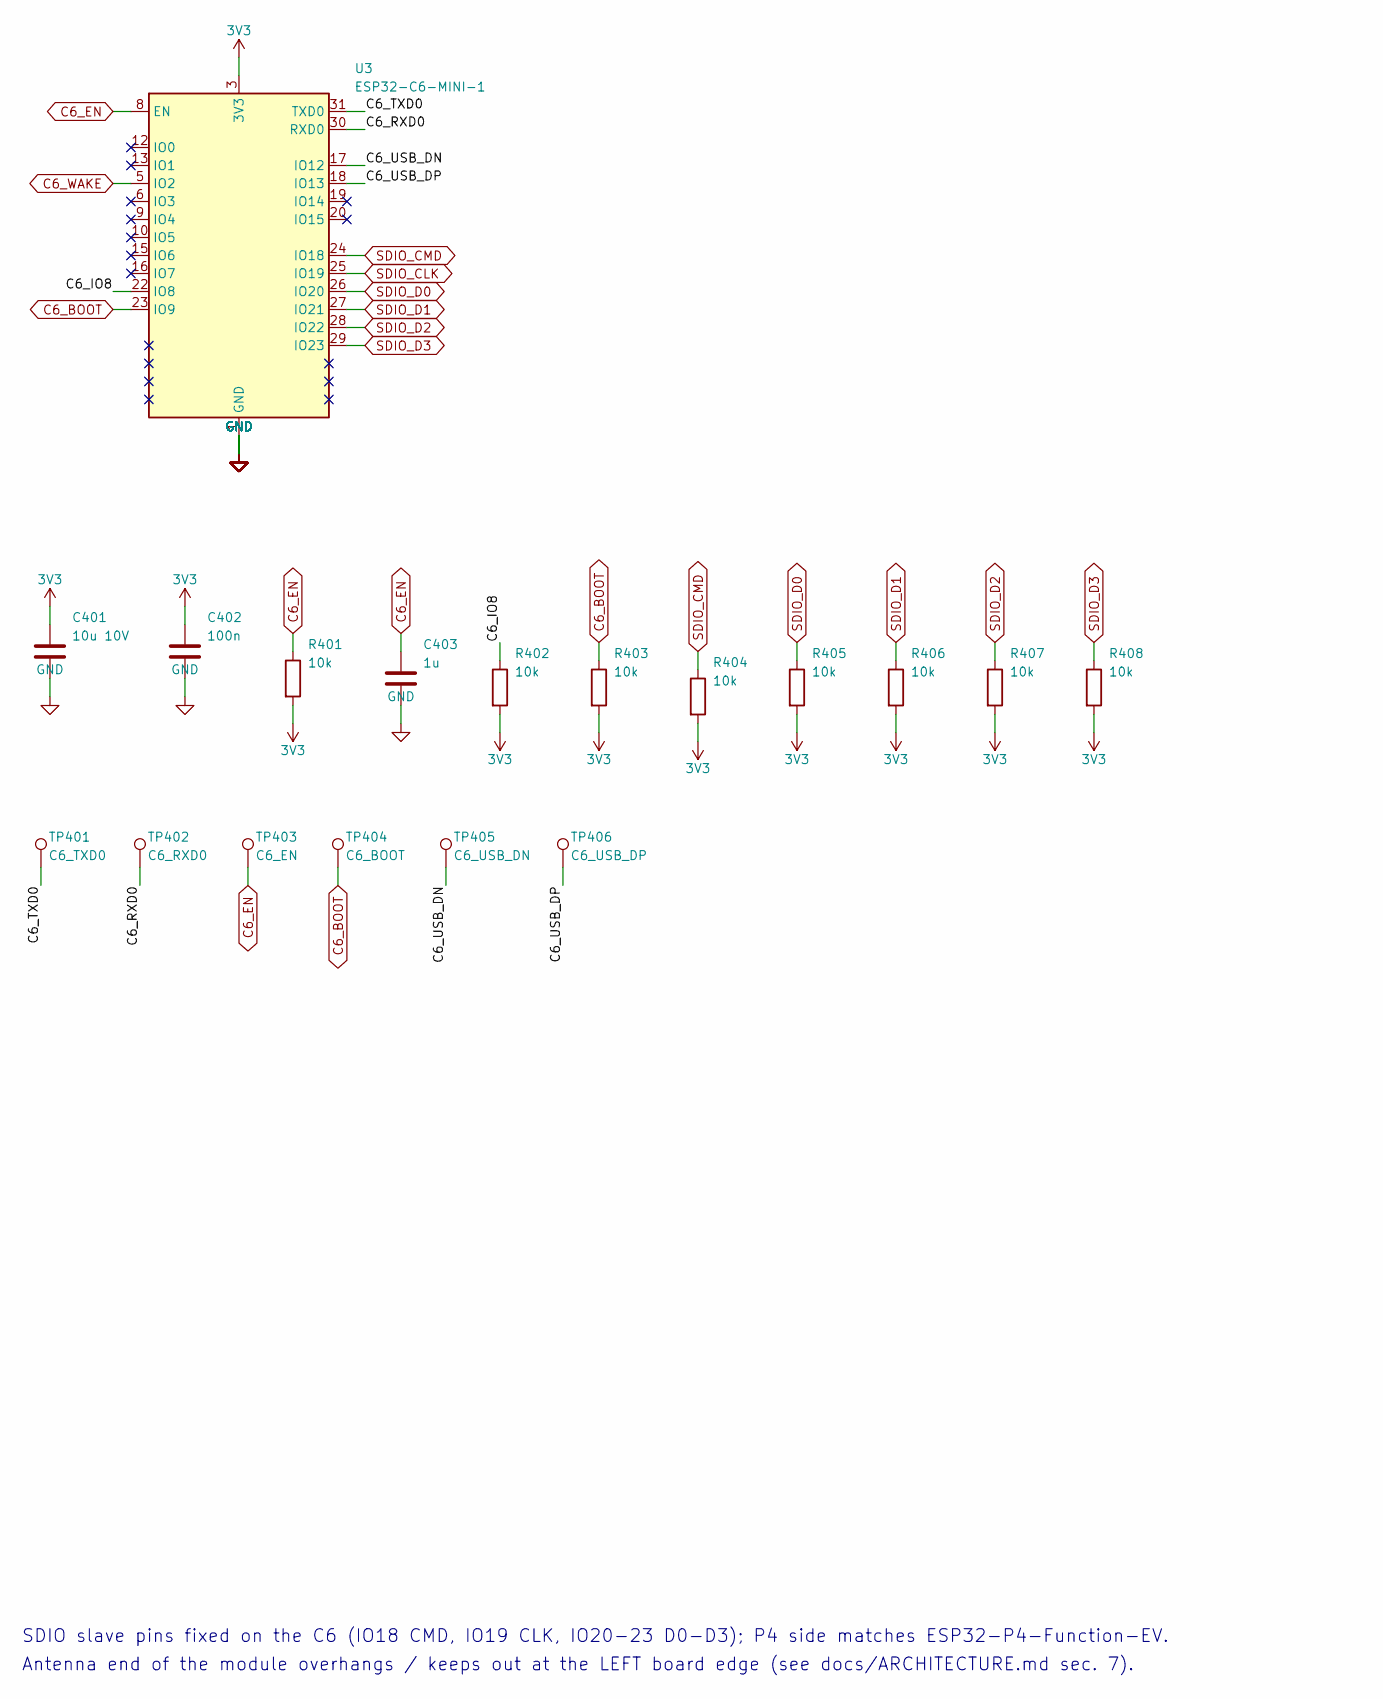
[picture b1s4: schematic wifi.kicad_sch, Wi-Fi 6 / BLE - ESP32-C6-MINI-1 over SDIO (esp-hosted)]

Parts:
C401: 10u 10V; C_0603_1608Metric; MPN CL10A106KP8NNNC; LCSC C19702
C402: 100n; C_0402_1005Metric; MPN CL05B104KO5NNNC; LCSC C1525
C403: 1u; C_0402_1005Metric; MPN CL05A105KA5NQNC; LCSC C52923
R401, R402, R403, R404, R405, R406, R407, R408: 10k; R_0402_1005Metric; MPN 0402WGF1002TCE; LCSC C25744
TP401: C6_TXD0; TestPoint_Pad_D1.0mm
TP402: C6_RXD0; TestPoint_Pad_D1.0mm
TP403: C6_EN; TestPoint_Pad_D1.0mm
TP404: C6_BOOT; TestPoint_Pad_D1.0mm
TP405: C6_USB_DN; TestPoint_Pad_D1.0mm
TP406: C6_USB_DP; TestPoint_Pad_D1.0mm
U3: ESP32-C6-MINI-1; MPN ESP32-C6-MINI-1-N4; LCSC C5453904

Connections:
3V3: C401.1, C402.1, R401.2, R402.2, R403.2, R404.2, R405.2, R406.2, R407.2, R408.2, U3.3 (3V3); also elsewhere on the board
/wifi/C6_IO8: R402.1, U3.22 (IO8)
/wifi/C6_RXD0: TP402.1, U3.30 (RXD0)
/wifi/C6_TXD0: TP401.1, U3.31 (TXD0)
/wifi/C6_USB_DN: TP405.1, U3.17 (IO12)
/wifi/C6_USB_DP: TP406.1, U3.18 (IO13)
C6_BOOT: R403.1, TP404.1, U3.23 (IO9); also elsewhere on the board
C6_EN: C403.1, R401.1, TP403.1, U3.8 (EN); also elsewhere on the board
C6_WAKE: U3.5 (IO2); also elsewhere on the board
GND: C401.2, C402.2, C403.2, U3.1 (GND), U3.2 (GND), U3.11 (GND), U3.14 (GND), U3.36 (GND), U3.37 (GND), U3.38 (GND), U3.39 (GND), U3.40 (GND), U3.41 (GND), U3.42 (GND), U3.43 (GND), U3.44 (GND), U3.45 (GND), U3.46 (GND), U3.47 (GND), U3.48 (GND), U3.49 (GND), U3.50 (GND), U3.51 (GND), U3.52 (GND), U3.53 (GND); also elsewhere on the board
SDIO_CLK: U3.25 (IO19); also elsewhere on the board
SDIO_CMD: R404.1, U3.24 (IO18); also elsewhere on the board
SDIO_D0: R405.1, U3.26 (IO20); also elsewhere on the board
SDIO_D1: R406.1, U3.27 (IO21); also elsewhere on the board
SDIO_D2: R407.1, U3.28 (IO22); also elsewhere on the board
SDIO_D3: R408.1, U3.29 (IO23); also elsewhere on the board

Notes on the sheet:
SDIO slave pins fixed on the C6 (IO18 CMD, IO19 CLK, IO20-23 D0-D3); P4 side matches ESP32-P4-Function-EV.
Antenna end of the module overhangs / keeps out at the LEFT board edge (see docs/ARCHITECTURE.md sec. 7).
